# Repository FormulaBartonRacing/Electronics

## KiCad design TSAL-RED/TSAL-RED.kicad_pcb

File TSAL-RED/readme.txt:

v1.0
------
Location: Inside TS enclosure

- RED LED Driver
- TSAL outputs (both LEDs)
- Discharge circuit
- TSMP Connector

Discharge Circuit
-----------------
R = 1.2k
C = 4418 uF
Discharge time to 60V from 118V is about 3.6s
Peak power across R = ~12W

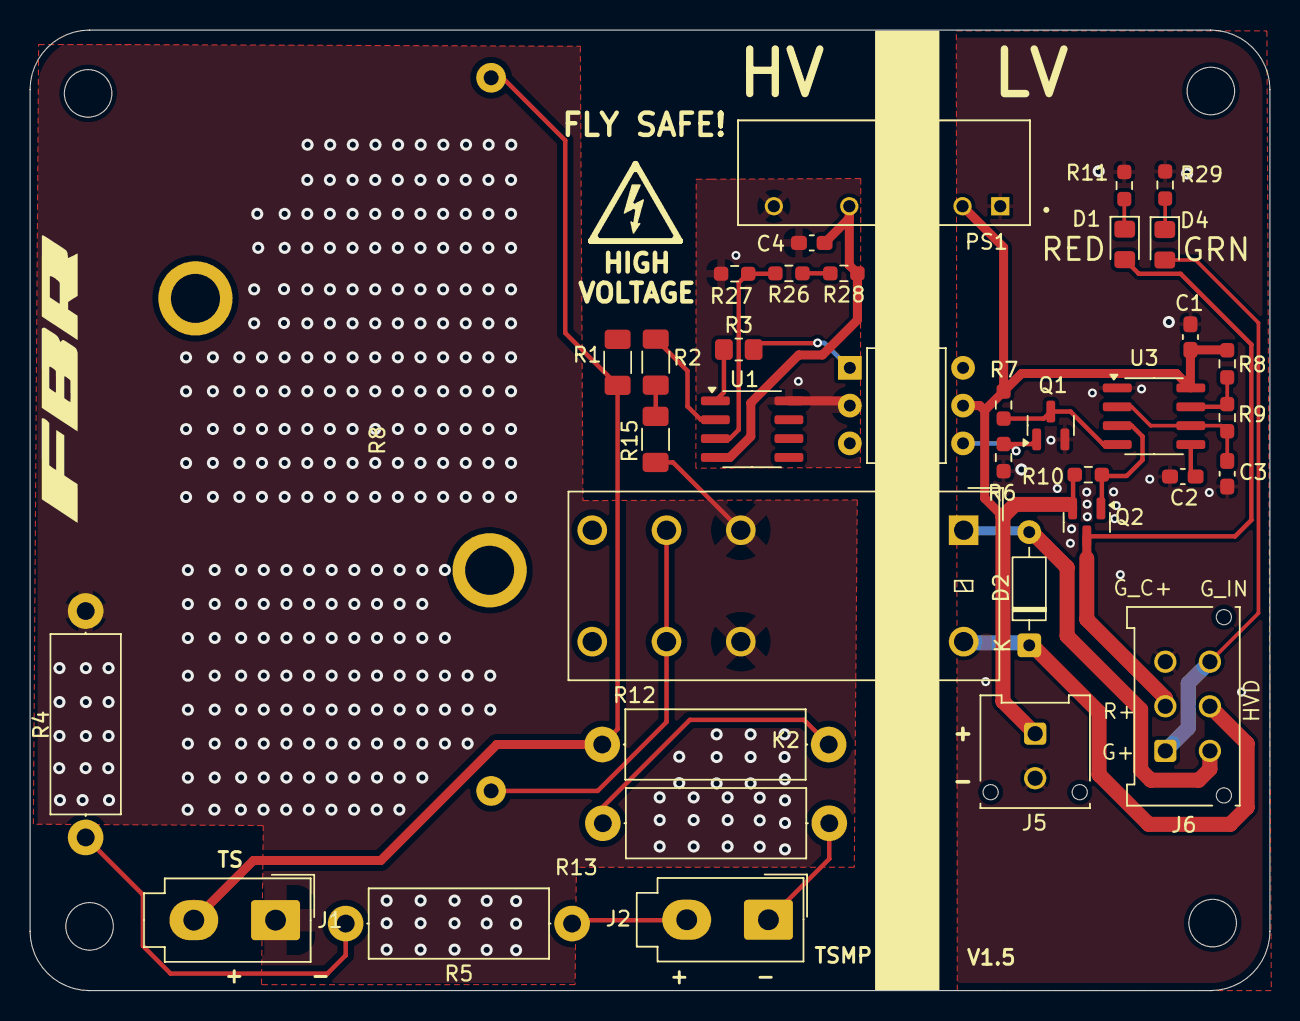
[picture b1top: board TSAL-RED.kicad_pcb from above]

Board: 2 copper layers, 83.5 x 64.7 mm, 41 parts (0 on the bottom side), 29 nets.

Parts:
C1, C2, C4: 0.1uF; C_0603_1608Metric_Pad1.08x0.95mm_HandSolder
C3: 1u; C_0603_1608Metric_Pad1.08x0.95mm_HandSolder
D1: VHI; LED_0805_2012Metric_Pad1.15x1.40mm_HandSolder
D2: 1N4148; D_DO-35_SOD27_P7.62mm_Horizontal
D4: GRN; LED_0805_2012Metric_Pad1.15x1.40mm_HandSolder
H1, H2, H3, H4: MountingHole; MountingHole_3.2mm_M3_DIN965
J1, J2: Conn_01x02; Molex_Mini-Fit_Jr_5566-02A_2x01_P4.20mm_Vertical
J5: Conn_02x01; Molex_Micro-Fit_3.0_43045-0212_2x01_P3.00mm_Vertical
J6: Conn_02x03_Counter_Clockwise; Molex_Micro-Fit_3.0_43045-0612_2x03_P3.00mm_Vertical
K2: G2RL-1-E; Relay_DPDT_Omron_G2RL-2
PS1: RKZE-1205S_HP; CONV_RKZE-1205S_HP
Q1: 2N7002; SOT-23
Q2: AO3401A; SOT-23
R1: 330K; R_1206_3216Metric_Pad1.30x1.75mm_HandSolder
R2: 12K; R_1206_3216Metric_Pad1.30x1.75mm_HandSolder
R3: 1K; R_0805_2012Metric_Pad1.20x1.40mm_HandSolder
R4, R12: 2.2K; R_Axial_DIN0414_L11.9mm_D4.5mm_P15.24mm_Horizontal
R5, R13: 2.7K; R_Axial_DIN0414_L11.9mm_D4.5mm_P15.24mm_Horizontal
R6: 12k; R_0603_1608Metric_Pad0.98x0.95mm_HandSolder
R7: 33K; R_0603_1608Metric_Pad0.98x0.95mm_HandSolder
R8: 22k; R_0603_1608Metric_Pad0.98x0.95mm_HandSolder
R9: 220k; R_0603_1608Metric_Pad0.98x0.95mm_HandSolder
R10: 10k; R_0603_1608Metric_Pad0.98x0.95mm_HandSolder
R11, R29: 2k2; R_0603_1608Metric_Pad0.98x0.95mm_HandSolder
R14: 1.2K; HSA25
R15: 150; R_1206_3216Metric_Pad1.30x1.75mm_HandSolder
R26: 18K; R_0603_1608Metric_Pad0.98x0.95mm_HandSolder
R27: 10K; R_0603_1608Metric_Pad0.98x0.95mm_HandSolder
R28: 180; R_0603_1608Metric_Pad0.98x0.95mm_HandSolder
U1: LM358; SOIC-8_3.9x4.9mm_P1.27mm
U2: 4N35; DIP-6_W7.62mm
U3: NE555D; SOIC-8_3.9x4.9mm_P1.27mm

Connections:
/5V+_Iso: C4.1, PS1.5 (-VOUT), R28.1, U1.4 (V-)
/5V-_Iso: C4.2, PS1.7 (+VOUT), R27.2, U1.8 (V+), U2.2
/AIR_Sup+: D2.1 (K), J6.5, K2.A2
/GRN+: D4.2 (A), J6.1, J6.6
/RED+: D1.2 (A), J6.2, Q2.3 (D)
/TSAC_GLV-: D2.2 (A), J6.4, K2.A1
/V_Cap: R1.1, R2.1, U1.2 (-)
/Vref: R26.2, R27.1, U1.3 (+)
GLV+: C1.1, J5.1, PS1.2 (-VIN), Q2.2 (S), R7.1, R8.2, R10.2, U2.5, U3.8 (VCC)
GLV-: C1.2, C2.2, C3.1, J5.2, J6.3, PS1.1 (+VIN), Q1.2 (S), R6.2, R11.2, R29.2, U3.1 (GND)
unnamed: D1.1 (K), R11.1
unnamed: D4.1 (K), R29.1
unnamed: J2.1, R13.1
unnamed: J2.2, R5.1
unnamed: K2.11, K2.21, R14.2
unnamed: Q1.3 (D), R7.2, U3.4 (R)
unnamed: Q1.1 (G), R6.1, U2.4
unnamed: Q2.1 (G), R10.1, U3.3 (Q)
unnamed: R3.1, U1.1
unnamed: R3.2, U2.1
unnamed: R4.1, R5.2
unnamed: R12.1, R13.2
unnamed: R2.2, R15.1
unnamed: R26.1, R28.2
unnamed: C2.1, U3.5 (CV)
unnamed: R8.1, R9.2, U3.7 (DIS)
unnamed: C3.2, R9.1, U3.2 (TR), U3.6 (THR)
TS+: J1.2, R1.2, R12.2, R14.1
TS-: J1.1, K2.12, K2.22, R4.2, R15.2

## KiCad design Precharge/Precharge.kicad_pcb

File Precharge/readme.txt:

v3.2
-----
For use with Kelly KDHE controller with 4418 uF capacitance

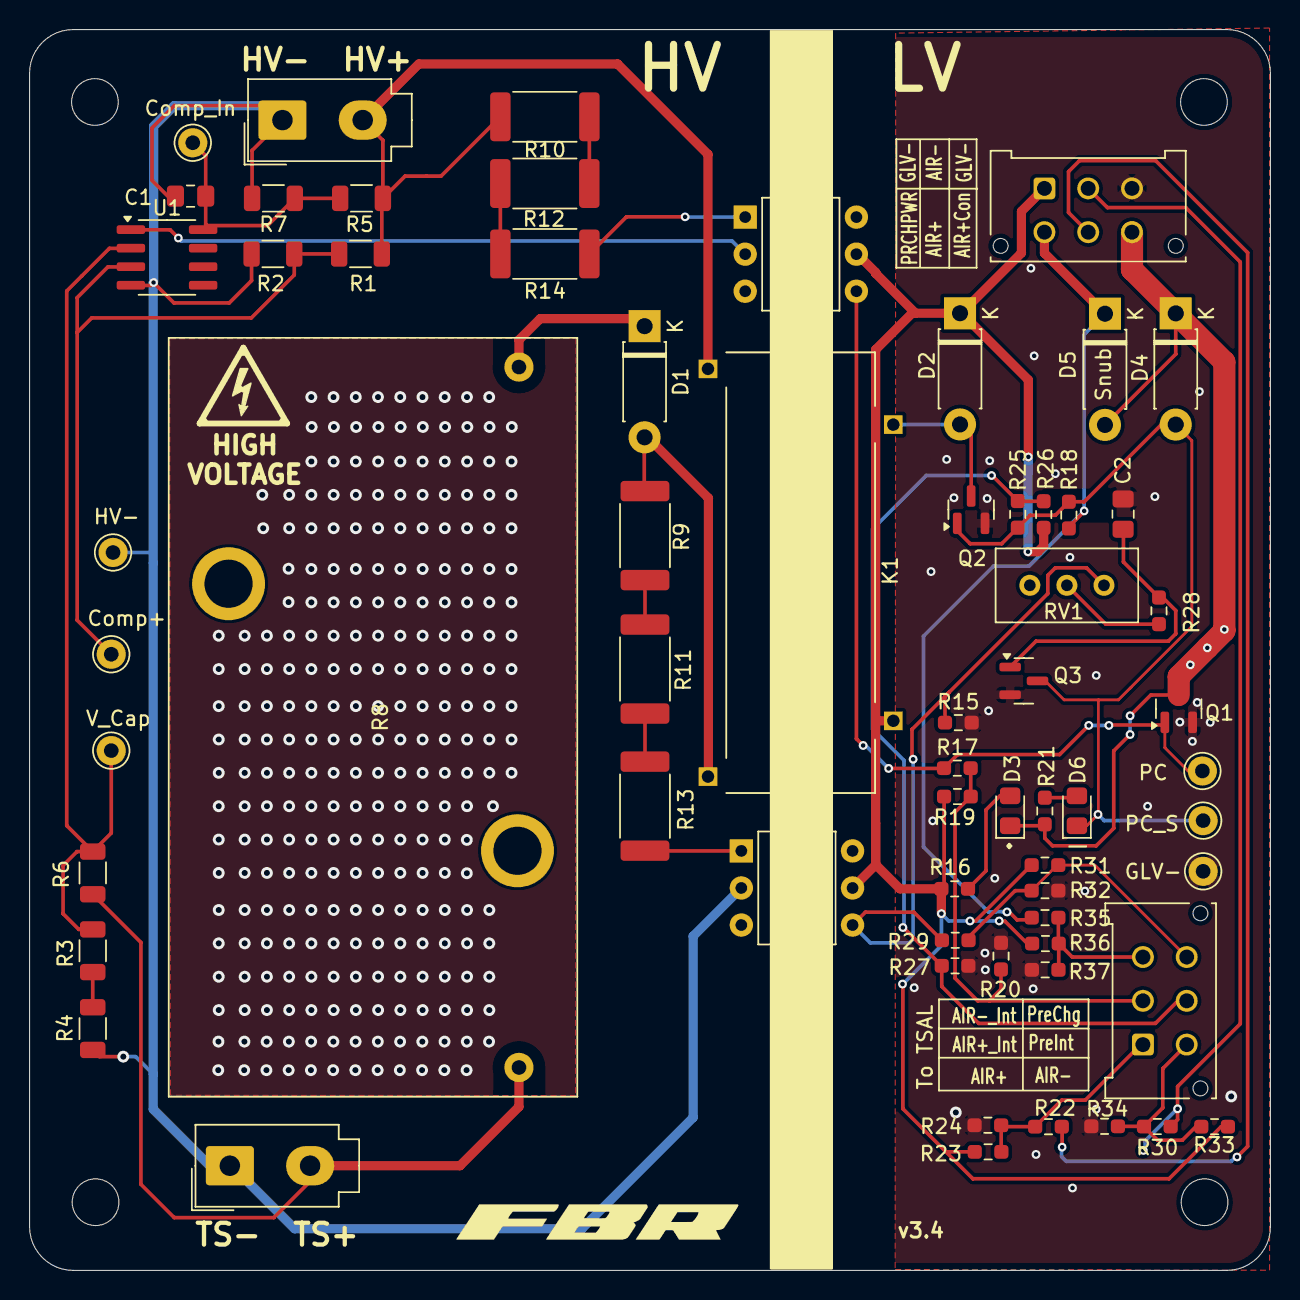
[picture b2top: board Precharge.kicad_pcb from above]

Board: 2 copper layers, 85.0 x 85.0 mm, 68 parts (0 on the bottom side), 36 nets.

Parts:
C1: 0.1 uF; C_0805_2012Metric_Pad1.18x1.45mm_HandSolder
C2: 10uF; C_0805_2012Metric_Pad1.18x1.45mm_HandSolder
D1, D2: 1n4937; D_DO-41_SOD81_P7.62mm_Horizontal
D3: P_C LED; LED_0805_2012Metric_Pad1.15x1.40mm_HandSolder
D4, D5: 1N4937; D_DO-41_SOD81_P7.62mm_Horizontal
D6: P_F LED; LED_0805_2012Metric_Pad1.15x1.40mm_HandSolder
H1, H2, H3, H4: MountingHole; MountingHole_3.2mm_M3_DIN965
J1, J2: Conn_01x02; Molex_Mini-Fit_Jr_5566-02A_2x01_P4.20mm_Vertical
J3: Molex MicroFit; Molex_Micro-Fit_3.0_43045-0612_2x03_P3.00mm_Vertical
J4: Conn_02x03_Counter_Clockwise; Molex_Micro-Fit_3.0_43045-0612_2x03_P3.00mm_Vertical
K1: KT12-1A-40L-THT; RELAY_KT12-1A-40L-THT
Q1: CJ2310; SOT-23
Q2, Q3: AO3400A; SOT-23
R1, R6: 330K; R_1206_3216Metric
R2, R3: 10K; R_1206_3216Metric
R4: 270; R_1206_3216Metric
R5: 15K; R_1206_3216Metric
R7: 1.5K; R_1206_3216Metric
R8: 150; HSA25
R9, R10, R11, R12, R13, R14: 3.3K; R_2512_6332Metric_Pad1.40x3.35mm_HandSolder
R15, R18: 10K; R_0603_1608Metric_Pad0.98x0.95mm_HandSolder
R16, R21: 1.8K; R_0603_1608Metric_Pad0.98x0.95mm_HandSolder
R17, R22, R29, R30, R35: 18K; R_0603_1608Metric_Pad0.98x0.95mm_HandSolder
R19, R23, R26, R31, R33, R36: 75K; R_0603_1608Metric_Pad0.98x0.95mm_HandSolder
R20, R24, R27, R32, R34, R37: 8.6K; R_0603_1608Metric_Pad0.98x0.95mm_HandSolder
R25: 7.5K; R_0603_1608Metric_Pad0.98x0.95mm_HandSolder
R28: 1.5Meg; R_0603_1608Metric_Pad0.98x0.95mm_HandSolder
RV1: R_Potentiometer_Trim; Potentiometer_Bourns_3296W_Vertical
TP1, TP2, TP3, TP4: TestPoint; Pin_D1.0mm_L10.0mm
TP5: TestPoint P_C; Pin_D1.0mm_L10.0mm
TP6: GLV-; Pin_D1.0mm_L10.0mm
TP7: Prech_Shut; Pin_D1.0mm_L10.0mm
U1: LM393; SOIC-8_3.9x4.9mm_P1.27mm
U3, U4: 4N35; DIP-6_W7.62mm

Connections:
/AIR+: J4.1, R22.2, R23.2, R24.1
/AIR+_GND: D3.1 (K), D4.1 (K), D5.2 (A), J3.6, Q1.3 (D), R21.2
/AIR+_Int: J4.2, R17.2, R19.2, R20.1
/AIR+_Out: J3.5, R22.1
/AIR-: J4.4, R30.2, R33.2, R34.1
/AIR-_Int: J4.3, R35.2, R36.2, R37.1
/AIR-_Out: J3.2, R30.1
/AIR_Sup+: D5.1 (K), J3.4, R18.2, R35.1
/Comp_Out: U1.1, U4.2
/PreCh_Complt: Q1.1 (G), R17.1, TP5.1, U4.4
/PreCh_Int: J4.5, R25.2, R26.2, R27.1
/Precharge: J4.6, R29.2, R31.2, R32.1
/Precharge_12V: R15.1, R29.1, RV1.1, U3.4
/V_Accu: R1.1, R2.2, TP1.1, U1.3 (+)
/V_Cap: R3.1, R6.2, TP2.1, U1.2 (-)
GLV+: D2.1 (K), J3.1, K1.COIL2, R16.2, R19.1, R23.1, R26.1, R31.1, R33.1, R36.1, U3.5, U4.5
GLV-: C2.2, J3.3, Q1.2 (S), Q2.2 (S), Q3.2 (S), R15.2, R20.2, R24.2, R27.2, R32.2, R34.2, R37.2, TP6.1
HV+: J1.2, K1.NO, R1.2, R5.2, R10.2
HV-: C1.2, J1.1, J2.1, R2.1, R4.2, R7.1, TP3.1, U1.4 (V-), U3.2
unnamed: D1.2 (A), K1.COM, R9.2
unnamed: D1.1 (K), R8.1
unnamed: D2.2 (A), K1.COIL1, Q2.3 (D)
unnamed: D3.2 (A), R16.1
unnamed: D4.2 (A), D6.1 (K), Q2.1 (G), Q3.3 (D), R18.1, R25.1, TP7.1
unnamed: D6.2 (A), R21.1
unnamed: J2.2, R6.1, R8.2
unnamed: C2.1, Q3.1 (G), R28.2
unnamed: R3.2, R4.1
unnamed: R10.1, R12.1
unnamed: R9.1, R11.1
unnamed: R11.2, R13.1
unnamed: R12.2, R14.1
unnamed: R13.2, U3.1
unnamed: R14.2, U4.1
unnamed: R28.1, RV1.2
unnamed: C1.1, R5.1, R7.2, TP4.1, U1.8 (V+)

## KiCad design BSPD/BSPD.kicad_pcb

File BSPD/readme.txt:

Current Sensor - LEM HTFS 400-P
For 117.6V max voltage, 5kW corresponds to 42.5A

Ipn = 400A
Uref = 2.5V (For 5V supply)
Uout = Uref ± (1.25 . Ip/Ipn)
=> Uout = 2.63V for 42.5A input

Set pot R5 to >= 9k ohm

References:
https://www.lem.com/sites/default/files/products_datasheets/htfs_200_800-p.pdf

https://www.formulastudent.de/fileadmin/user_upload/all/2020/important_docs/ESF/Example_BSPD_V2.pdf

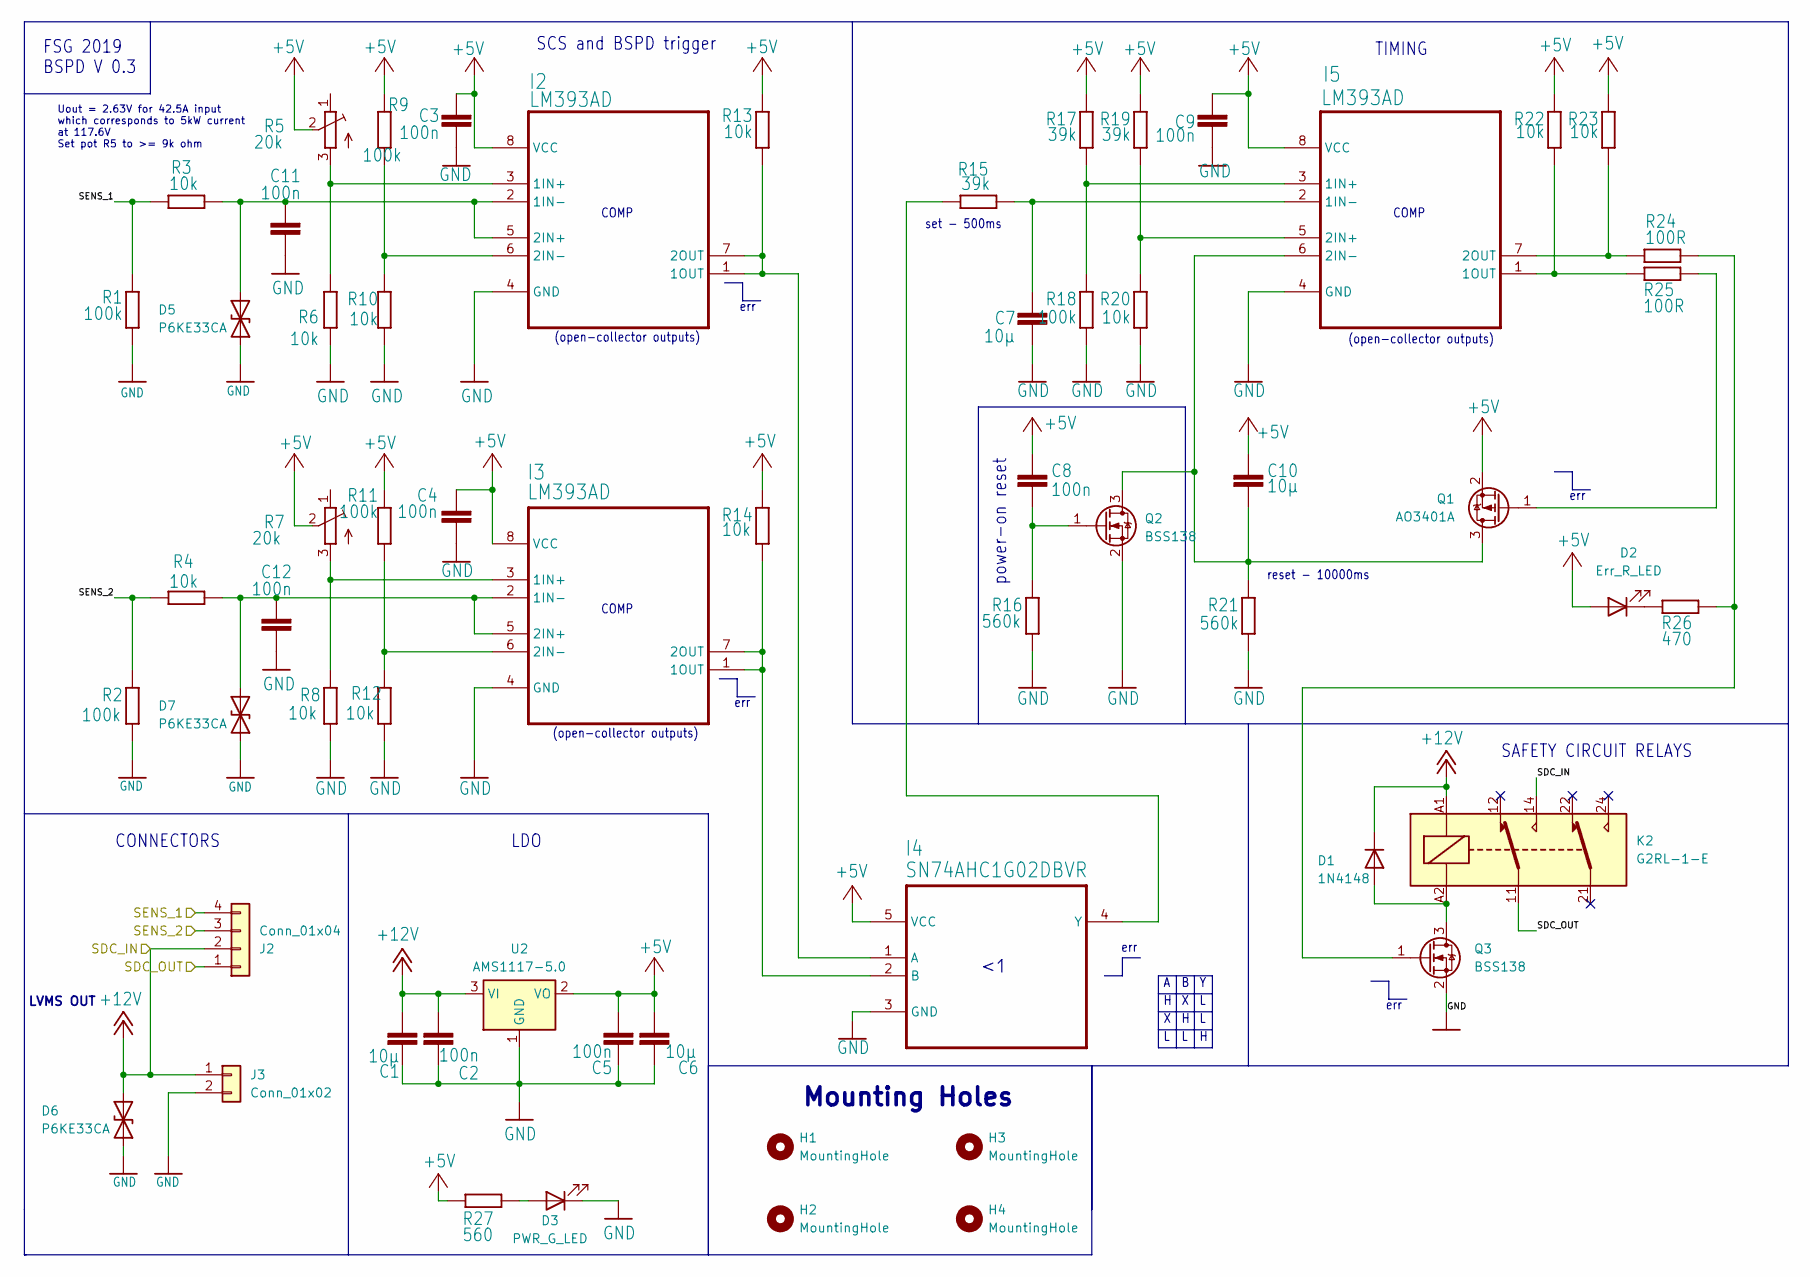
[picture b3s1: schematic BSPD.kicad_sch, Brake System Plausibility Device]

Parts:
C1, C6, C7: 10µ; C_0603_1608Metric_Pad1.08x0.95mm_HandSolder
C2, C3, C4, C5, C8, C9, C11, C12: 100n; C_0603_1608Metric_Pad1.08x0.95mm_HandSolder
C10: 10µ; C_Elec_5x5.4
D1: 1N4148; D_DO-35_SOD27_P7.62mm_Horizontal
D2: Err_R_LED; LED_0603_1608Metric_Pad1.05x0.95mm_HandSolder
D3: PWR_G_LED; LED_0603_1608Metric_Pad1.05x0.95mm_HandSolder
D5, D6, D7: P6KE33CA; D_DO-15_P12.70mm_Horizontal
H1, H2, H3, H4: MountingHole; MountingHole_3.2mm_M3_DIN965
I2, I3, I5: LM393AD; SOIC-8_3.9x4.9mm_P1.27mm
I4: SN74AHC1G02DBVR; SOT-23-5
J2: Conn_01x04; Molex_KK-396_5273-04A_1x04_P3.96mm_Vertical
J3: Conn_01x02; Molex_KK-396_5273-02A_1x02_P3.96mm_Vertical
K2: G2RL-1-E; Relay_DPDT_Omron_G2RL-2
Q1: AO3401A; SOT-23
Q2, Q3: BSS138; SOT-23
R1, R2, R9, R11, R18: 100k; R_0603_1608Metric_Pad0.98x0.95mm_HandSolder
R3, R4, R6, R8, R10, R12, R13, R14, R20, R22, R23: 10k; R_0603_1608Metric_Pad0.98x0.95mm_HandSolder
R5, R7: 20k; Potentiometer_Bourns_3296W_Vertical
R15, R17, R19: 39k; R_0603_1608Metric_Pad0.98x0.95mm_HandSolder
R16, R21: 560k; R_0603_1608Metric_Pad0.98x0.95mm_HandSolder
R24, R25: 100R; R_0603_1608Metric_Pad0.98x0.95mm_HandSolder
R26: 470; R_0603_1608Metric_Pad0.98x0.95mm_HandSolder
R27: 560; R_0603_1608Metric_Pad0.98x0.95mm_HandSolder
U2: AMS1117-5.0; SOT-223-3_TabPin2

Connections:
+5V: C3.2, C4.2, C5.2, C6.1, C8.1, C9.2, C10.1, D2.2 (A), I2.8 (VCC), I3.8 (VCC), I4.5 (VCC), I5.8 (VCC), Q1.2 (S), R5.2 (M), R7.2 (M), R9.1, R11.1, R13.1, R14.1, R17.2, R19.2, R22.2, R23.2, R27.2, U2.2 (VO)
+12V: C1.1, C2.1, D1.1 (K), D6.2 (A2), J2.2, J3.1, K2.14, K2.A1, U2.3 (VI)
/SDC_OUT: J2.1, K2.11
/SENS_1: J2.4, R1.2, R3.1
/SENS_2: J2.3, R2.2, R4.1
GND: C1.2, C2.2, C3.1, C4.1, C5.1, C6.2, C7.2, C9.1, C11.1, C12.1, D3.1 (K), D5.1 (A1), D6.1 (A1), D7.1 (A1), I2.4 (GND), I3.4 (GND), I4.3 (GND), I5.4 (GND), J3.2, Q2.2 (S), Q3.2 (S), R1.1, R2.1, R6.2, R8.2, R10.2, R12.2, R16.1, R18.1, R20.1, R21.1, U2.1 (GND)
unnamed: D1.2 (A), K2.A2, Q3.3 (D)
unnamed: D2.1 (K), R26.2
unnamed: D3.2 (A), R27.1
unnamed: C11.2, D5.2 (A2), I2.2 (1IN-), I2.5 (2IN+), R3.2
unnamed: C12.2, D7.2 (A2), I3.2 (1IN-), I3.5 (2IN+), R4.2
unnamed: I2.3 (1IN+), R5.3 (A), R6.1
unnamed: I2.1 (1OUT), I2.7 (2OUT), I4.1 (A), R13.2
unnamed: I2.6 (2IN-), R9.2, R10.1
unnamed: I3.3 (1IN+), R7.3 (A), R8.1
unnamed: I3.1 (1OUT), I3.7 (2OUT), I4.2 (B), R14.2
unnamed: I3.6 (2IN-), R11.2, R12.1
unnamed: I4.4 (Y), R15.2
unnamed: I5.3 (1IN+), R17.1, R18.2
unnamed: C7.1, I5.2 (1IN-), R15.1
unnamed: I5.1 (1OUT), R22.1, R25.2
unnamed: I5.5 (2IN+), R19.1, R20.2
unnamed: C10.2, I5.6 (2IN-), Q1.3 (D), Q2.3 (D), R21.2
unnamed: I5.7 (2OUT), R23.1, R24.2
unnamed: Q1.1 (G), R25.1
unnamed: C8.2, Q2.1 (G), R16.2
unnamed: Q3.1 (G), R24.1, R26.1

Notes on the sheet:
(open-collector outputs)
LVMS OUT
err
Uout = 2.63V for 42.5A input which corresponds to 5kW current at 117.6V Set pot R5 to >= 9k ohm
CONNECTORS
set - 500ms
reset - 10000ms
COMP
FSG 2019 BSPD V 0.3
power-on reset
SAFETY CIRCUIT RELAYS
LDO
SCS and BSPD trigger
Mounting Holes
TIMING

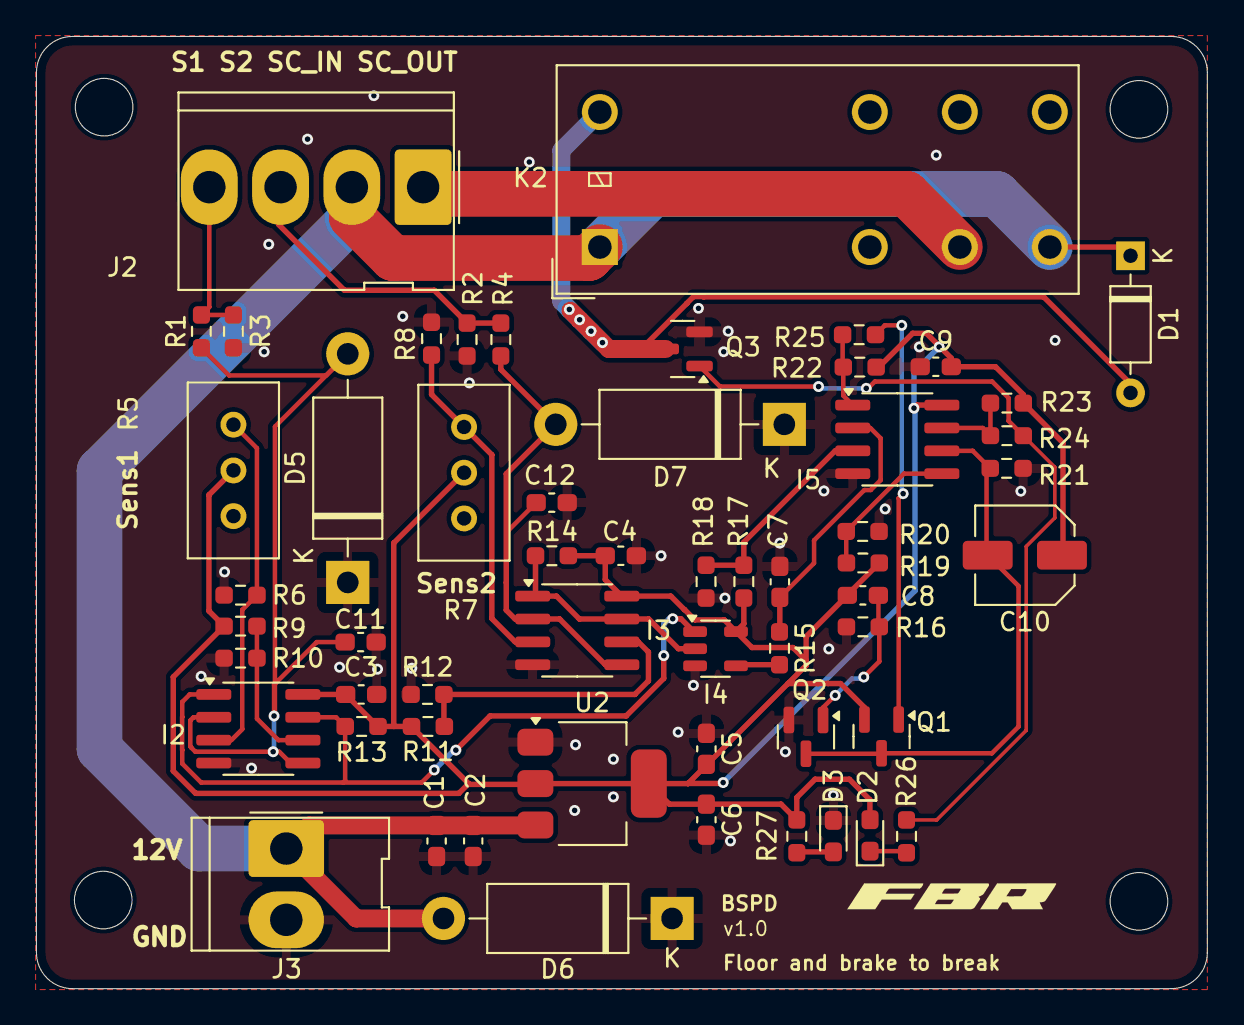
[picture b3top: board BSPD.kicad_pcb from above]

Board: 2 copper layers, 65.1 x 52.9 mm, 60 parts (0 on the bottom side), 27 nets.

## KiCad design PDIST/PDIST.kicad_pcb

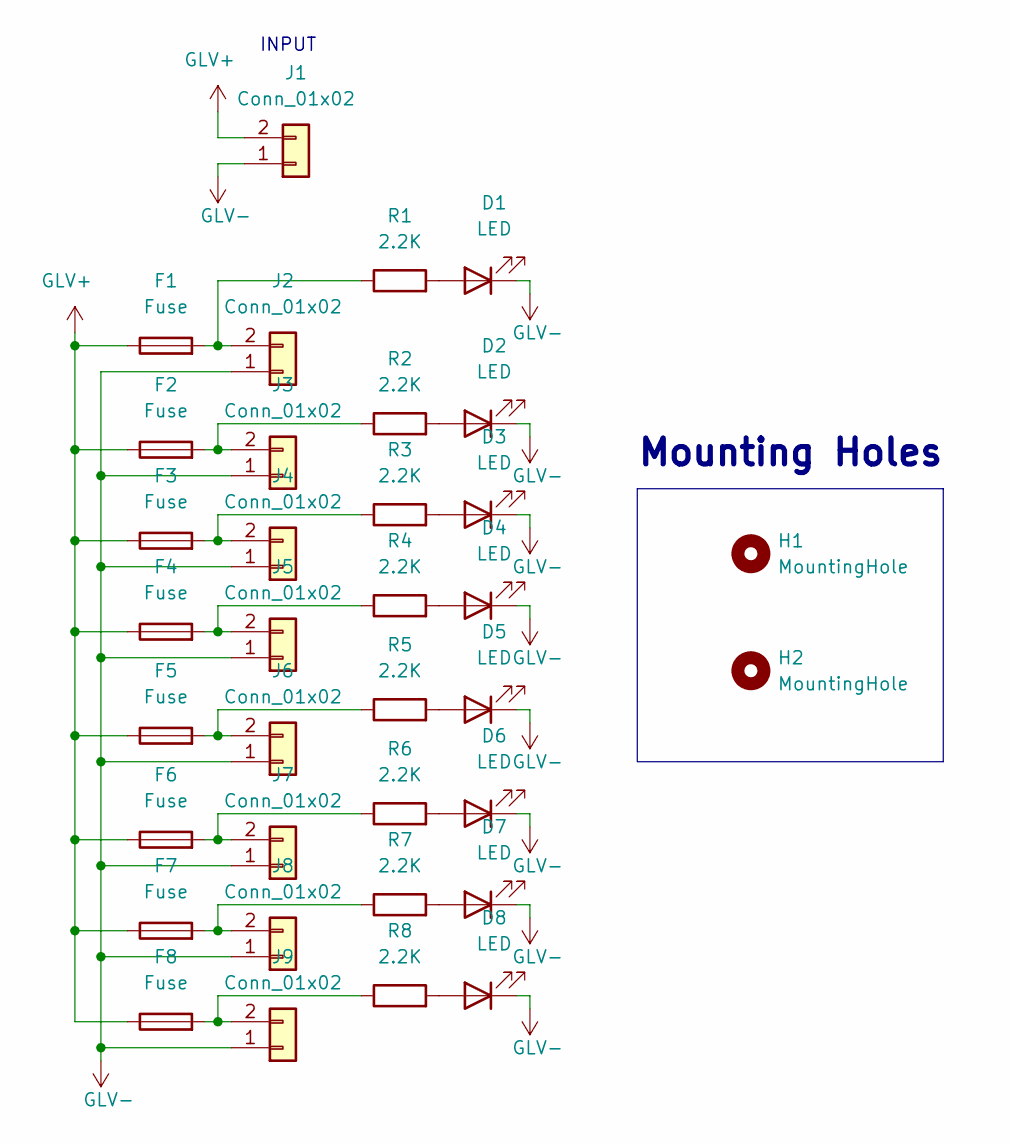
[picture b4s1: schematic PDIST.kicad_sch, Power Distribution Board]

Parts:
D1, D2, D3, D4, D5, D6, D7, D8: LED; LED_0603_1608Metric_Pad1.05x0.95mm_HandSolder
F1, F2, F3, F4, F5, F6, F7, F8: Fuse; Fuse_Littelfuse_372_D8.50mm
H1, H2: MountingHole; MountingHole_3.2mm_M3_DIN965
J1, J2, J3, J4, J5, J6, J7, J8, J9: Conn_01x02; Molex_Mini-Fit_Jr_5566-02A_2x01_P4.20mm_Vertical
R1, R2, R3, R4, R5, R6, R7, R8: 2.2K; R_0603_1608Metric_Pad0.98x0.95mm_HandSolder

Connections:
GLV+: F1.1, F2.1, F3.1, F4.1, F5.1, F6.1, F7.1, F8.1, J1.2
GLV-: D1.1 (K), D2.1 (K), D3.1 (K), D4.1 (K), D5.1 (K), D6.1 (K), D7.1 (K), D8.1 (K), J1.1, J2.1, J3.1, J4.1, J5.1, J6.1, J7.1, J8.1, J9.1
unnamed: D1.2 (A), R1.2
unnamed: D2.2 (A), R2.2
unnamed: D3.2 (A), R3.2
unnamed: D4.2 (A), R4.2
unnamed: D5.2 (A), R5.2
unnamed: D6.2 (A), R6.2
unnamed: D7.2 (A), R7.2
unnamed: D8.2 (A), R8.2
unnamed: F1.2, J2.2, R1.1
unnamed: F2.2, J3.2, R2.1
unnamed: F3.2, J4.2, R3.1
unnamed: F4.2, J5.2, R4.1
unnamed: F5.2, J6.2, R5.1
unnamed: F6.2, J7.2, R6.1
unnamed: F7.2, J8.2, R7.1
unnamed: F8.2, J9.2, R8.1

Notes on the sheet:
INPUT
Mounting Holes

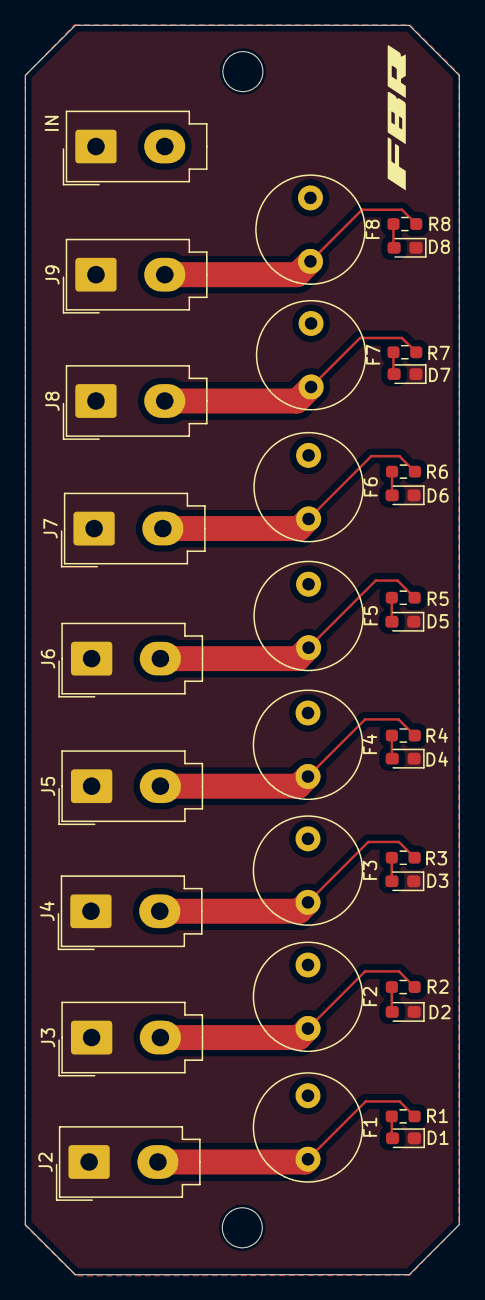
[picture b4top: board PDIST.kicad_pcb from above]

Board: 2 copper layers, 34.7 x 99.9 mm, 35 parts (0 on the bottom side), 18 nets.

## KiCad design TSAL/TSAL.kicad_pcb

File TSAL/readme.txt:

v1.0
-------
For GREEN LED driver

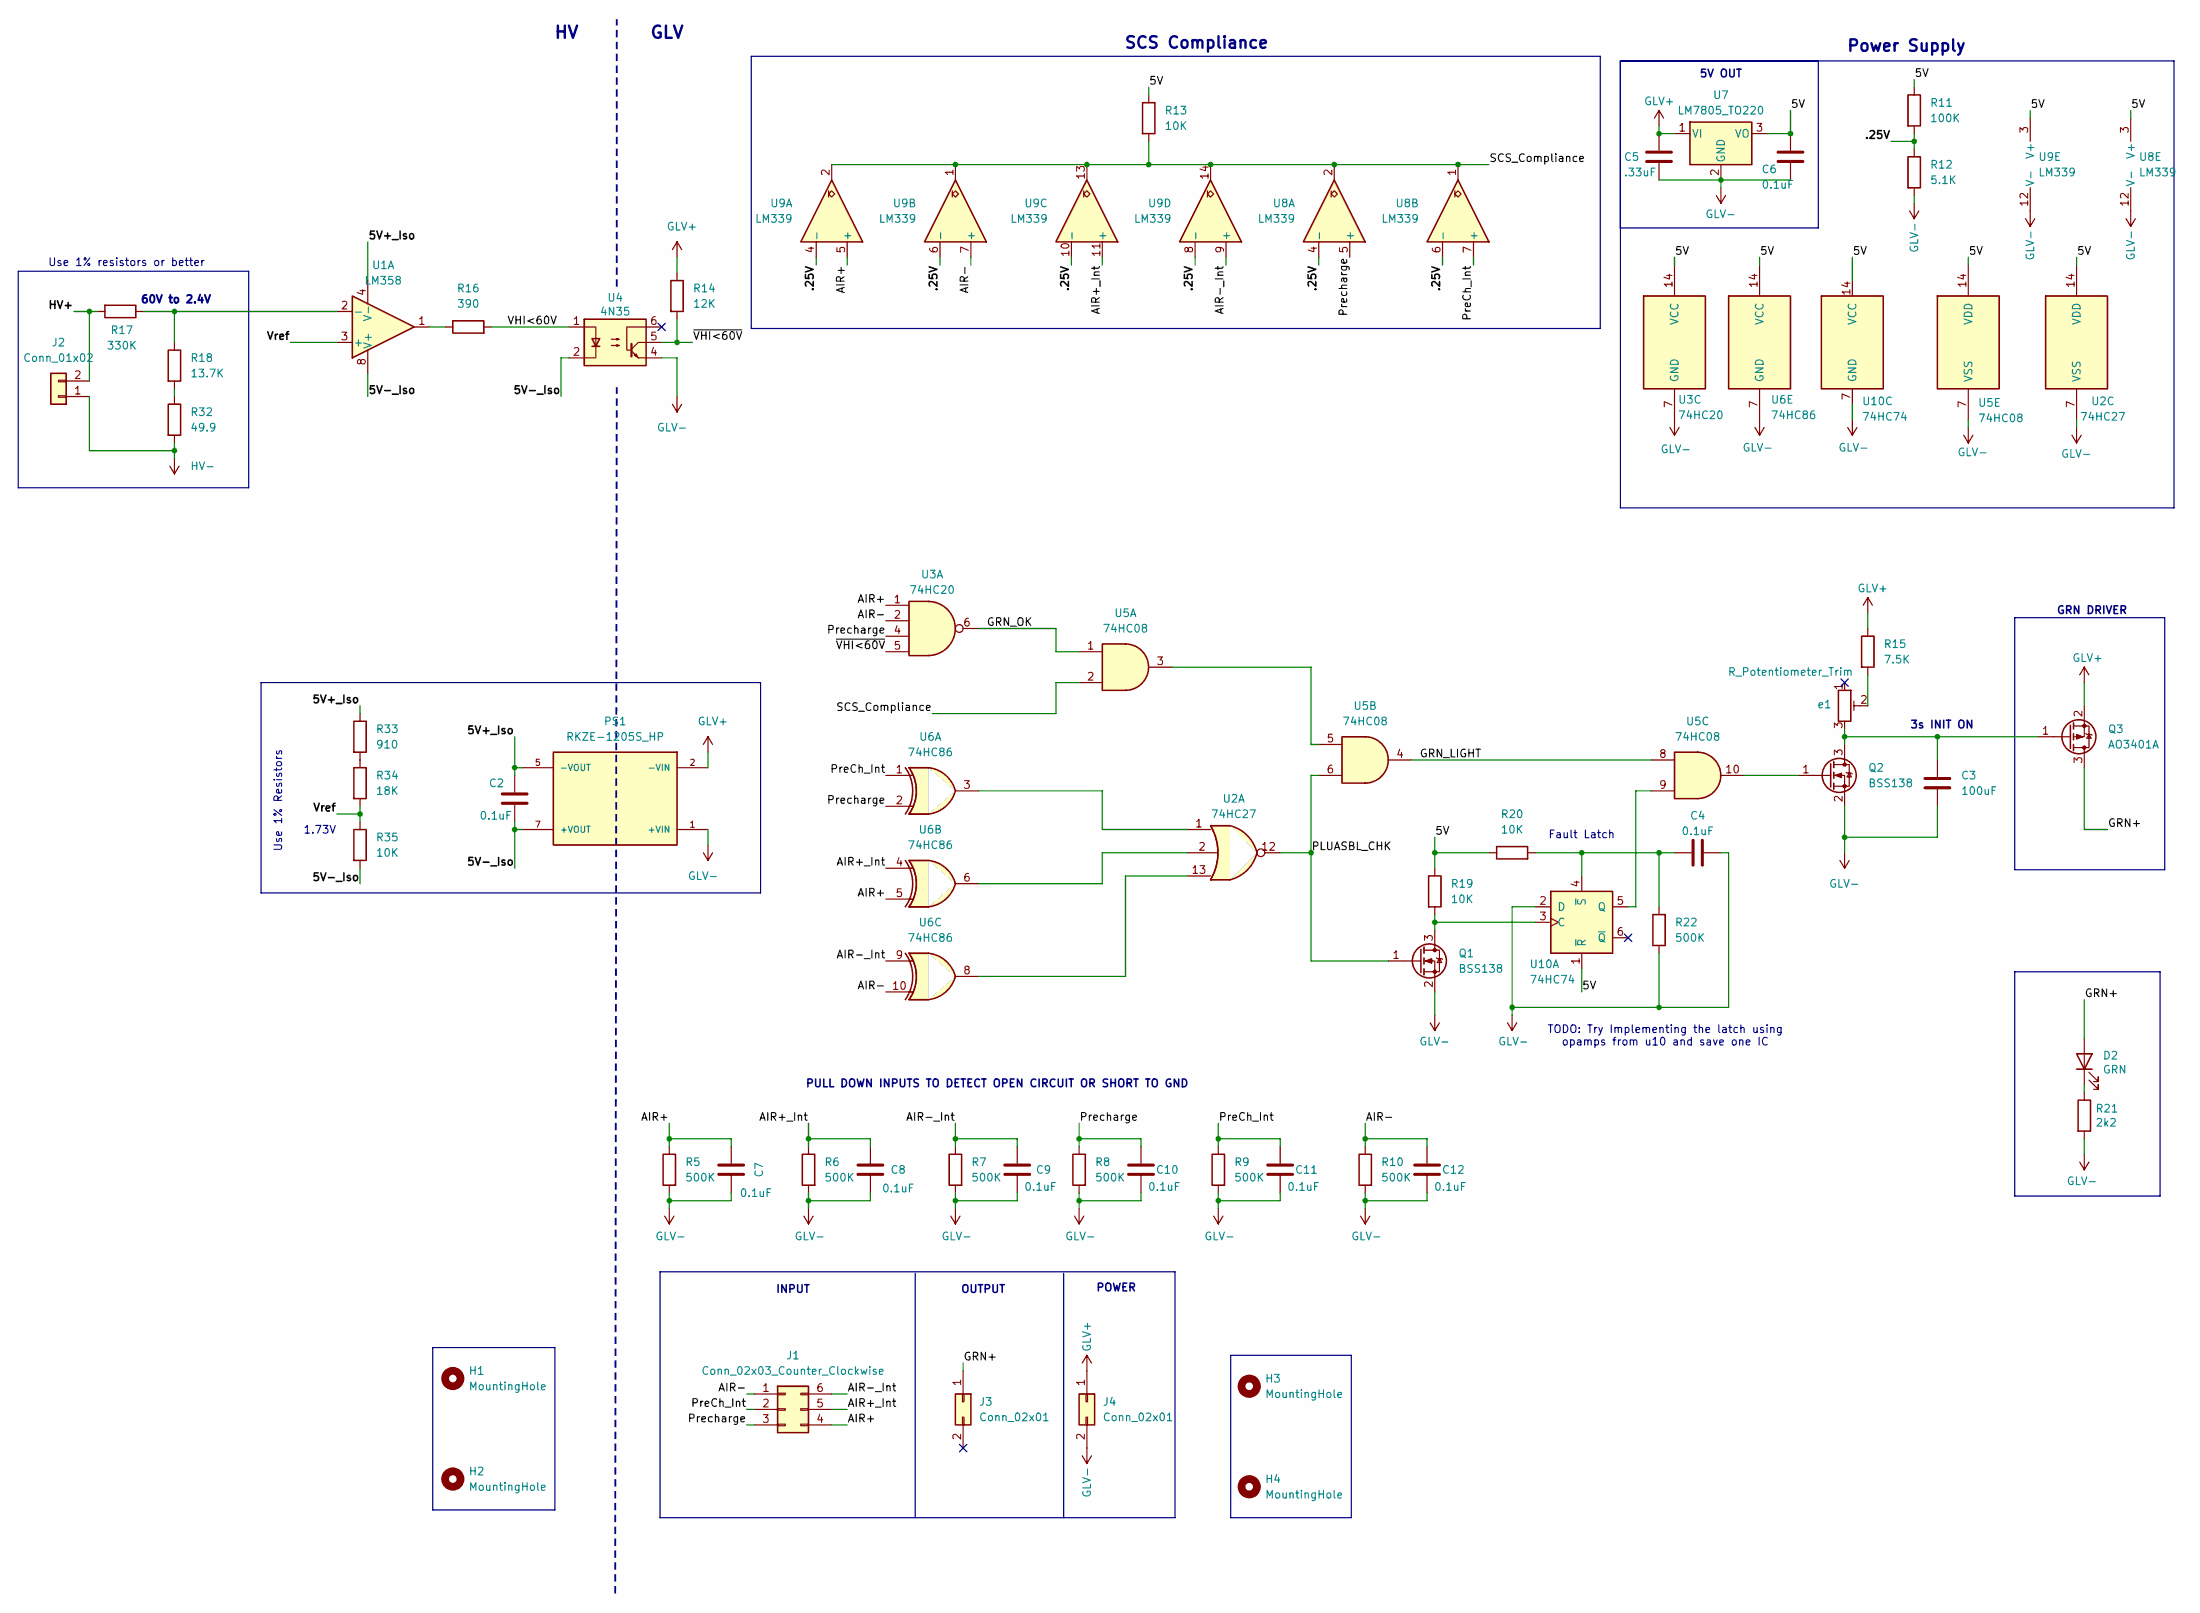
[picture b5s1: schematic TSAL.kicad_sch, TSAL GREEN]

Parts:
C2, C4, C6, C7, C8, C9, C10, C11, C12: 0.1uF; C_0603_1608Metric_Pad1.08x0.95mm_HandSolder
C3: 100uF; C_Elec_6.3x7.7
C5: .33uF; C_0603_1608Metric_Pad1.08x0.95mm_HandSolder
D2: GRN; LED_0805_2012Metric_Pad1.15x1.40mm_HandSolder
H1, H2, H3, H4: MountingHole; MountingHole_3.2mm_M3_DIN965
J1: Conn_02x03_Counter_Clockwise; Molex_Micro-Fit_3.0_43045-0612_2x03_P3.00mm_Vertical
J2: Conn_01x02; Molex_Mini-Fit_Jr_5566-02A_2x01_P4.20mm_Vertical
J3, J4: Conn_02x01; Molex_Micro-Fit_3.0_43045-0212_2x01_P3.00mm_Vertical
PS1: RKZE-1205S_HP; CONV_RKZE-1205S_HP
Q1, Q2: BSS138; SOT-23
Q3: AO3401A; SOT-23
R5, R6, R7, R8, R9, R10, R22: 500K; R_0603_1608Metric_Pad0.98x0.95mm_HandSolder
R11: 100K; R_0603_1608Metric_Pad0.98x0.95mm_HandSolder
R12: 5.1K; R_0603_1608Metric_Pad0.98x0.95mm_HandSolder
R13, R19, R20, R35: 10K; R_0603_1608Metric_Pad0.98x0.95mm_HandSolder
R14: 12K; R_0603_1608Metric_Pad0.98x0.95mm_HandSolder
R15: 7.5K; R_0603_1608Metric_Pad0.98x0.95mm_HandSolder
R16: 390; R_0603_1608Metric_Pad0.98x0.95mm_HandSolder
R17: 330K; R_1206_3216Metric_Pad1.30x1.75mm_HandSolder
R18: 13.7K; R_1206_3216Metric_Pad1.30x1.75mm_HandSolder
R21: 2k2; R_0603_1608Metric_Pad0.98x0.95mm_HandSolder
R32: 49.9; R_1206_3216Metric_Pad1.30x1.75mm_HandSolder
R33: 910; R_0603_1608Metric_Pad0.98x0.95mm_HandSolder
R34: 18K; R_0603_1608Metric_Pad0.98x0.95mm_HandSolder
U1: LM358; SOIC-8_3.9x4.9mm_P1.27mm
U2: 74HC27; SOIC-14_3.9x8.7mm_P1.27mm
U3: 74HC20; DIP-14_W7.62mm
U4: 4N35; DIP-6_W7.62mm
U5: 74HC08; DIP-14_W7.62mm
U6: 74HC86; DIP-14_W7.62mm
U7: LM7805_TO220; TO-220-3_Horizontal_TabDown
U8, U9: LM339; DIP-14_W7.62mm
U10: 74HC74; DIP-14_W7.62mm
e1: R_Potentiometer_Trim; Potentiometer_Bourns_3386F_Vertical

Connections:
/5V: C6.2, R11.1, R13.1, R19.1, R20.1, U2.14 (VDD), U3.14 (VCC), U5.14 (VDD), U6.14 (VCC), U7.3 (VO), U8.3 (V+), U9.3 (V+), U10.1 (~R), U10.14 (VCC)
/5V+_Iso: C2.1, PS1.5 (-VOUT), R33.1, U1.4 (V-)
/5V-_Iso: C2.2, PS1.7 (+VOUT), R35.2, U1.8 (V+), U4.2
/.25V: R11.2, R12.1, U8.4 (-), U8.6 (-), U9.4 (-), U9.6 (-), U9.8 (-), U9.10 (-)
/AIR+: C7.1, J1.4, R5.1, U3.1, U6.5, U9.5 (+)
/AIR+_Int: C8.1, J1.5, R6.1, U6.4, U9.11 (+)
/AIR-: C12.1, J1.1, R10.1, U3.2, U6.10, U9.7 (+)
/AIR-_Int: C9.1, J1.6, R7.1, U6.9, U9.9 (+)
/GRN+: D2.2 (A), J3.1, Q3.3 (D)
/GRN_LIGHT: U5.4, U5.8
/GRN_OK: U3.6, U5.1
/HV+: J2.2, R17.2
/PLUASBL_CHK: Q1.1 (G), U2.12, U5.6
/PreCh_Int: C11.1, J1.2, R9.1, U6.1, U8.7 (+)
/Precharge: C10.1, J1.3, R8.1, U3.4, U6.2, U8.5 (+)
/SCS_Compliance: R13.2, U5.2, U8.1, U8.2, U9.1, U9.2, U9.13, U9.14
/VHI<60V: R16.2, U4.1
/Vref: R34.2, R35.1, U1.3 (+)
/~VHI<60V: R14.2, U3.5, U4.5
GLV+: C5.1, J4.1, PS1.2 (-VIN), Q3.2 (S), R14.1, R15.1, U7.1 (VI)
GLV-: C3.2, C4.2, C5.2, C6.1, C7.2, C8.2, C9.2, C10.2, C11.2, C12.2, J4.2, PS1.1 (+VIN), Q1.2 (S), Q2.2 (S), R5.2, R6.2, R7.2, R8.2, R9.2, R10.2, R12.2, R21.2, R22.1, U2.7 (VSS), U3.7 (GND), U4.4, U5.7 (VSS), U6.7 (GND), U7.2 (GND), U8.12 (V-), U9.12 (V-), U10.2 (D), U10.7 (GND)
HV-: J2.1, R32.2
unnamed: D2.1 (K), R21.1
unnamed: Q1.3 (D), R19.2, U10.3 (C)
unnamed: C3.1, Q2.3 (D), Q3.1 (G), e1.3
unnamed: Q2.1 (G), U5.10
unnamed: R15.2, e1.2
unnamed: R16.1, U1.1
unnamed: R18.2, R32.1
unnamed: R33.2, R34.1
unnamed: R17.1, R18.1, U1.2 (-)
unnamed: U2.1, U6.3
unnamed: U2.2, U6.6
unnamed: U2.13, U6.8
unnamed: U5.3, U5.5
unnamed: U5.9, U10.5 (Q)
unnamed: C4.1, R20.2, R22.2, U10.4 (~S)

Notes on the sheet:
GLV
3s INIT ON
Power Supply
60V to 2.4V
GRN DRIVER
INPUT
TODO: Try Implementing the latch using opamps from u10 and save one IC
POWER
OUTPUT
PULL DOWN INPUTS TO DETECT OPEN CIRCUIT OR SHORT TO GND
Use 1% resistors or better
5V OUT
1.73V
SCS Compliance
Use 1% Resistors
Fault Latch

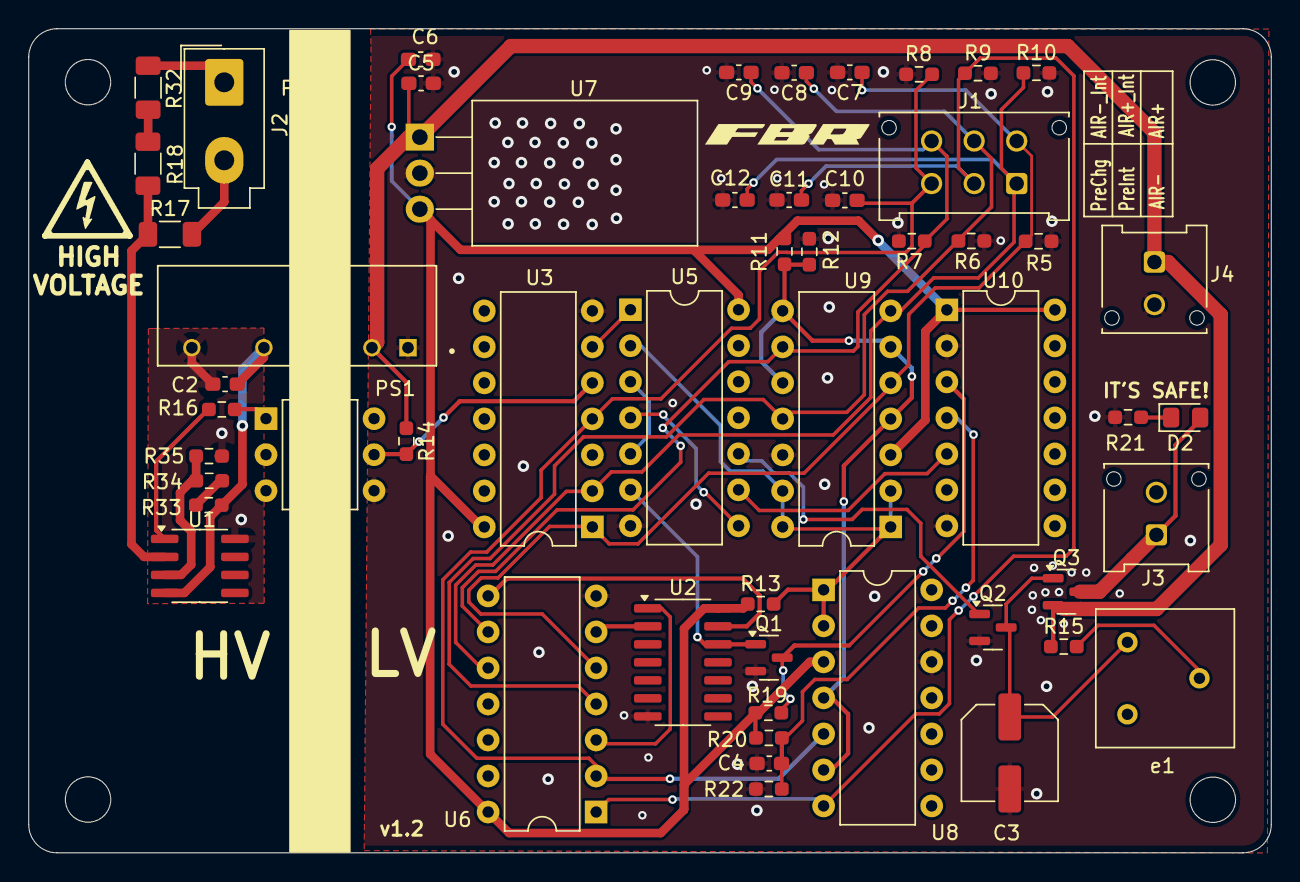
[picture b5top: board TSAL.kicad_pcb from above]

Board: 2 copper layers, 87.6 x 58.1 mm, 57 parts (0 on the bottom side), 37 nets.
